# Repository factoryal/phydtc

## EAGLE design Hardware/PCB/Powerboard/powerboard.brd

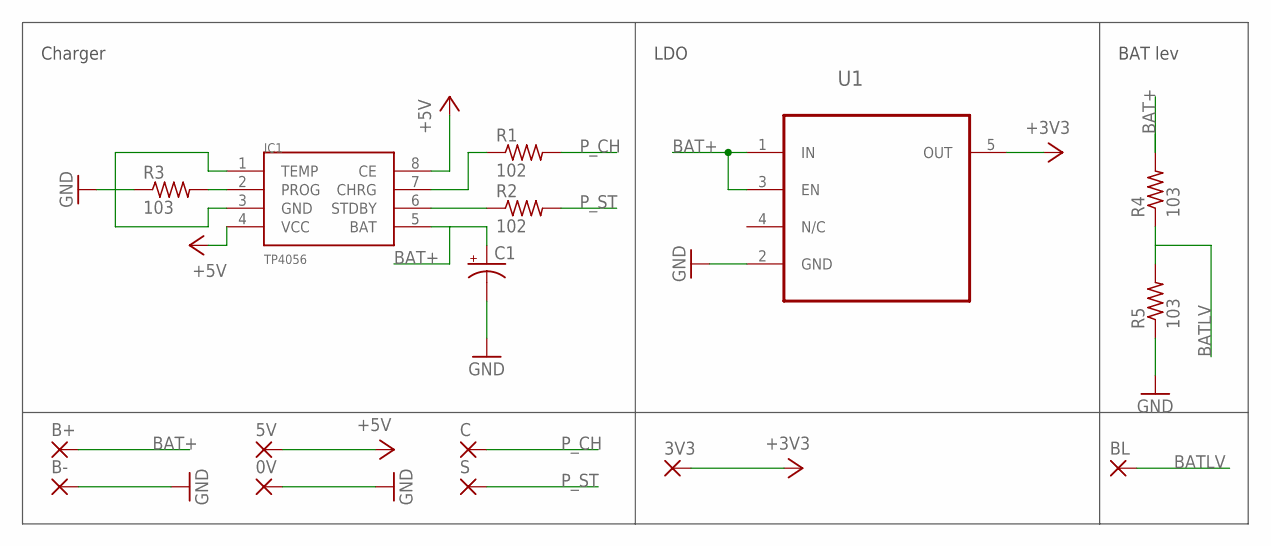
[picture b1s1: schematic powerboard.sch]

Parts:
0V, 3V3, 5V: SMD5; SMD2,54-5,08
B+: SMD5; SMD2,54-5,08
B-: SMD5; SMD2,54-5,08
BL: SMD5; SMD2,54-5,08
C: SMD5; SMD2,54-5,08
C1: CPOL-USR/2012-12R; R/2012-12R
IC1: TP4056; SOP-8
R1, R2: 102; M2012
R3, R4, R5: 103; M2012
S: SMD5; SMD2,54-5,08
U1: TLV70033DDCT; SOT95P280X110-5N

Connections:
+3V3: 3V3.1, U1.5 (OUT)
+5V: 5V.1, IC1.4 (VCC), IC1.8 (CE)
BAT+: B+.1, C1.+, IC1.5 (BAT), R4.2, U1.1 (IN), U1.3 (EN)
BATLV: BL.1, R4.1, R5.2
GND: 0V.1, B-.1, C1.-, IC1.1 (TEMP), IC1.3 (GND), R3.1, R5.1, U1.2 (GND)
unnamed: IC1.7 (CHRG), R1.1
unnamed: IC1.6 (STDBY), R2.1
unnamed: IC1.2 (PROG), R3.2
P_CH: C.1, R1.2
P_ST: R2.2, S.1

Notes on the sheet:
Charger
LDO
BAT lev

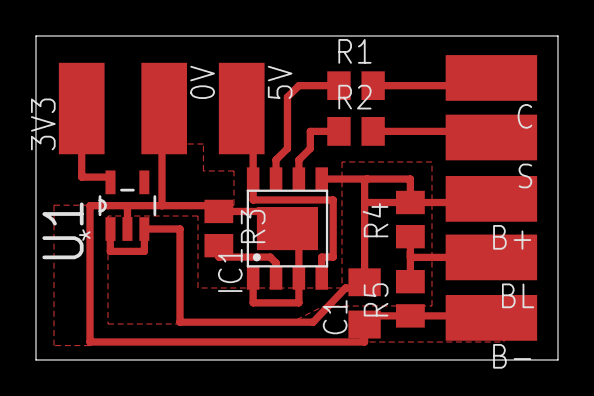
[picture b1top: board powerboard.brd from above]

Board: 2 copper layers, 29.0 x 18.0 mm, 16 parts (0 on the bottom side), 10 nets.

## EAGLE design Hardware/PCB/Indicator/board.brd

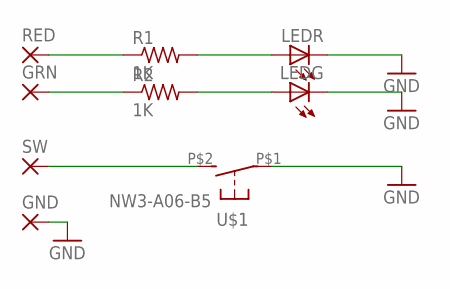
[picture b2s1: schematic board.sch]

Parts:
GND: SMD5; SMD2,54-5,08
GRN: SMD5; SMD2,54-5,08
LEDG: LEDCHIP-LED0805; CHIP-LED0805
LEDR: LEDCHIP-LED0805; CHIP-LED0805
R1, R2: 1K; M2012
RED: SMD5; SMD2,54-5,08
SW: SMD5; SMD2,54-5,08
U$1: NW3-A06-B5; DTSM-3-R

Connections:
GND: GND.1, LEDG.C, LEDR.C, U$1.P$1 (1)
unnamed: R1.1, RED.1
unnamed: GRN.1, R2.1
unnamed: LEDR.A, R1.2
unnamed: LEDG.A, R2.2
unnamed: SW.1, U$1.P$2 (2)

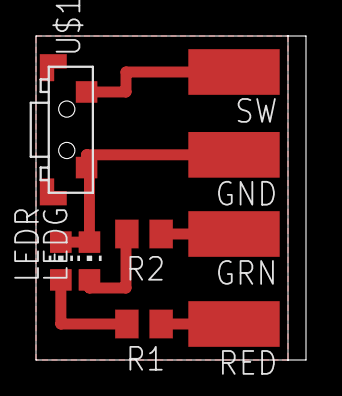
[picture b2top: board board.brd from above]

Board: 2 copper layers, 15.0 x 18.0 mm, 9 parts (0 on the bottom side), 6 nets.

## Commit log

2017-06-30 First commit
    Vector class complete
    Now configure 9-axis sensor class
2017-07-01 Directory configuration
    디렉토리 수정
2017-07-06 BT communication finish
    change switch pin 8 to 7
2017-07-06 bt-test
2017-07-06 Cloud Push
    백업용
2017-07-09 BT firmware included
    블루투스 펌웨어 및 매뉴얼 추가 및 클라우드 푸시
2017-07-10 Added nRF8001
    nRF8001과 관련된 파일 및 HM-10 펌웨어 수정
2017-07-17 nRF8001 removed
    MATLAB으로 읽어오는 센서 값이 튀는 현상을 수정해야 합니다.
2017-07-17 minor fix
    matlab buffer reduced
2017-07-21 Cloud Push
    Editing MATLAB Source Code
2017-07-21 Cloud Push
    MATLAB Source File Configured
2017-07-21 Cloud Push
    MATLAB Source File Modified
2017-07-21 Meeting Push
    MATLAB source file modified.
2017-07-27 android test code added
    Stupid Arduino Memory
2017-07-27 android test code added
2017-07-27 Android test code added
    shit arduino debugging
2017-07-31 MCU Multitask & PCB
    MCU - multitask method configured
    PCB - new added
2017-08-07 eagle file update
2017-08-07 Accelerometer Calibrated & MATLAB xyz
2017-08-07 PCB Inverted
2017-08-08 Cloud Push
2017-08-13 3d model added
2017-08-16 sensor filter applied
2017-08-17 Motion Count & Modeling
    - X-axis motion count feature release
    - Enclosure model updated
2017-08-17 Minor fix
    - commented android communication configuration and format
2017-08-18 Indicator board added
    - Indicator PCB design added
2017-08-22 cloud push
    - enclosure modeling updated
    - android communication protocol changed
    - io pcb board added
2017-08-25 cloud push
    - nRF8001 BT module migration progress
    - few screenshots
2017-08-28 cloud push
    - PCB size & pattern modified
    - Enclosure minor fix
2017-08-28 cloud push
    - enclosure v6 added
2017-08-30 Cloud push
    * MCU
    - new algorithm - ignoring unpatterned movement added
    * Enclosure
    - ver7 model added (indicator board insert problem modified)
2017-09-01 cloud push
    * Enclosure
    - minor fix
    * MCU
    - New android communication protol applying template added
    - New data logger database class added
2017-09-02 Cloud Push
    * MCU
    - database feature updated
2017-09-04 discard push
2017-09-05 Minor fix
2017-09-06 Cloud Push
    * MCU
    - Visual Studio InteliSense JAMMED.
    * Enclosure
    - minor fix
2017-09-08 Minor Commit
2017-09-26 cloud push
    MCU
    - DB algorithms configured
2018-02-25 Database Bug fixed
